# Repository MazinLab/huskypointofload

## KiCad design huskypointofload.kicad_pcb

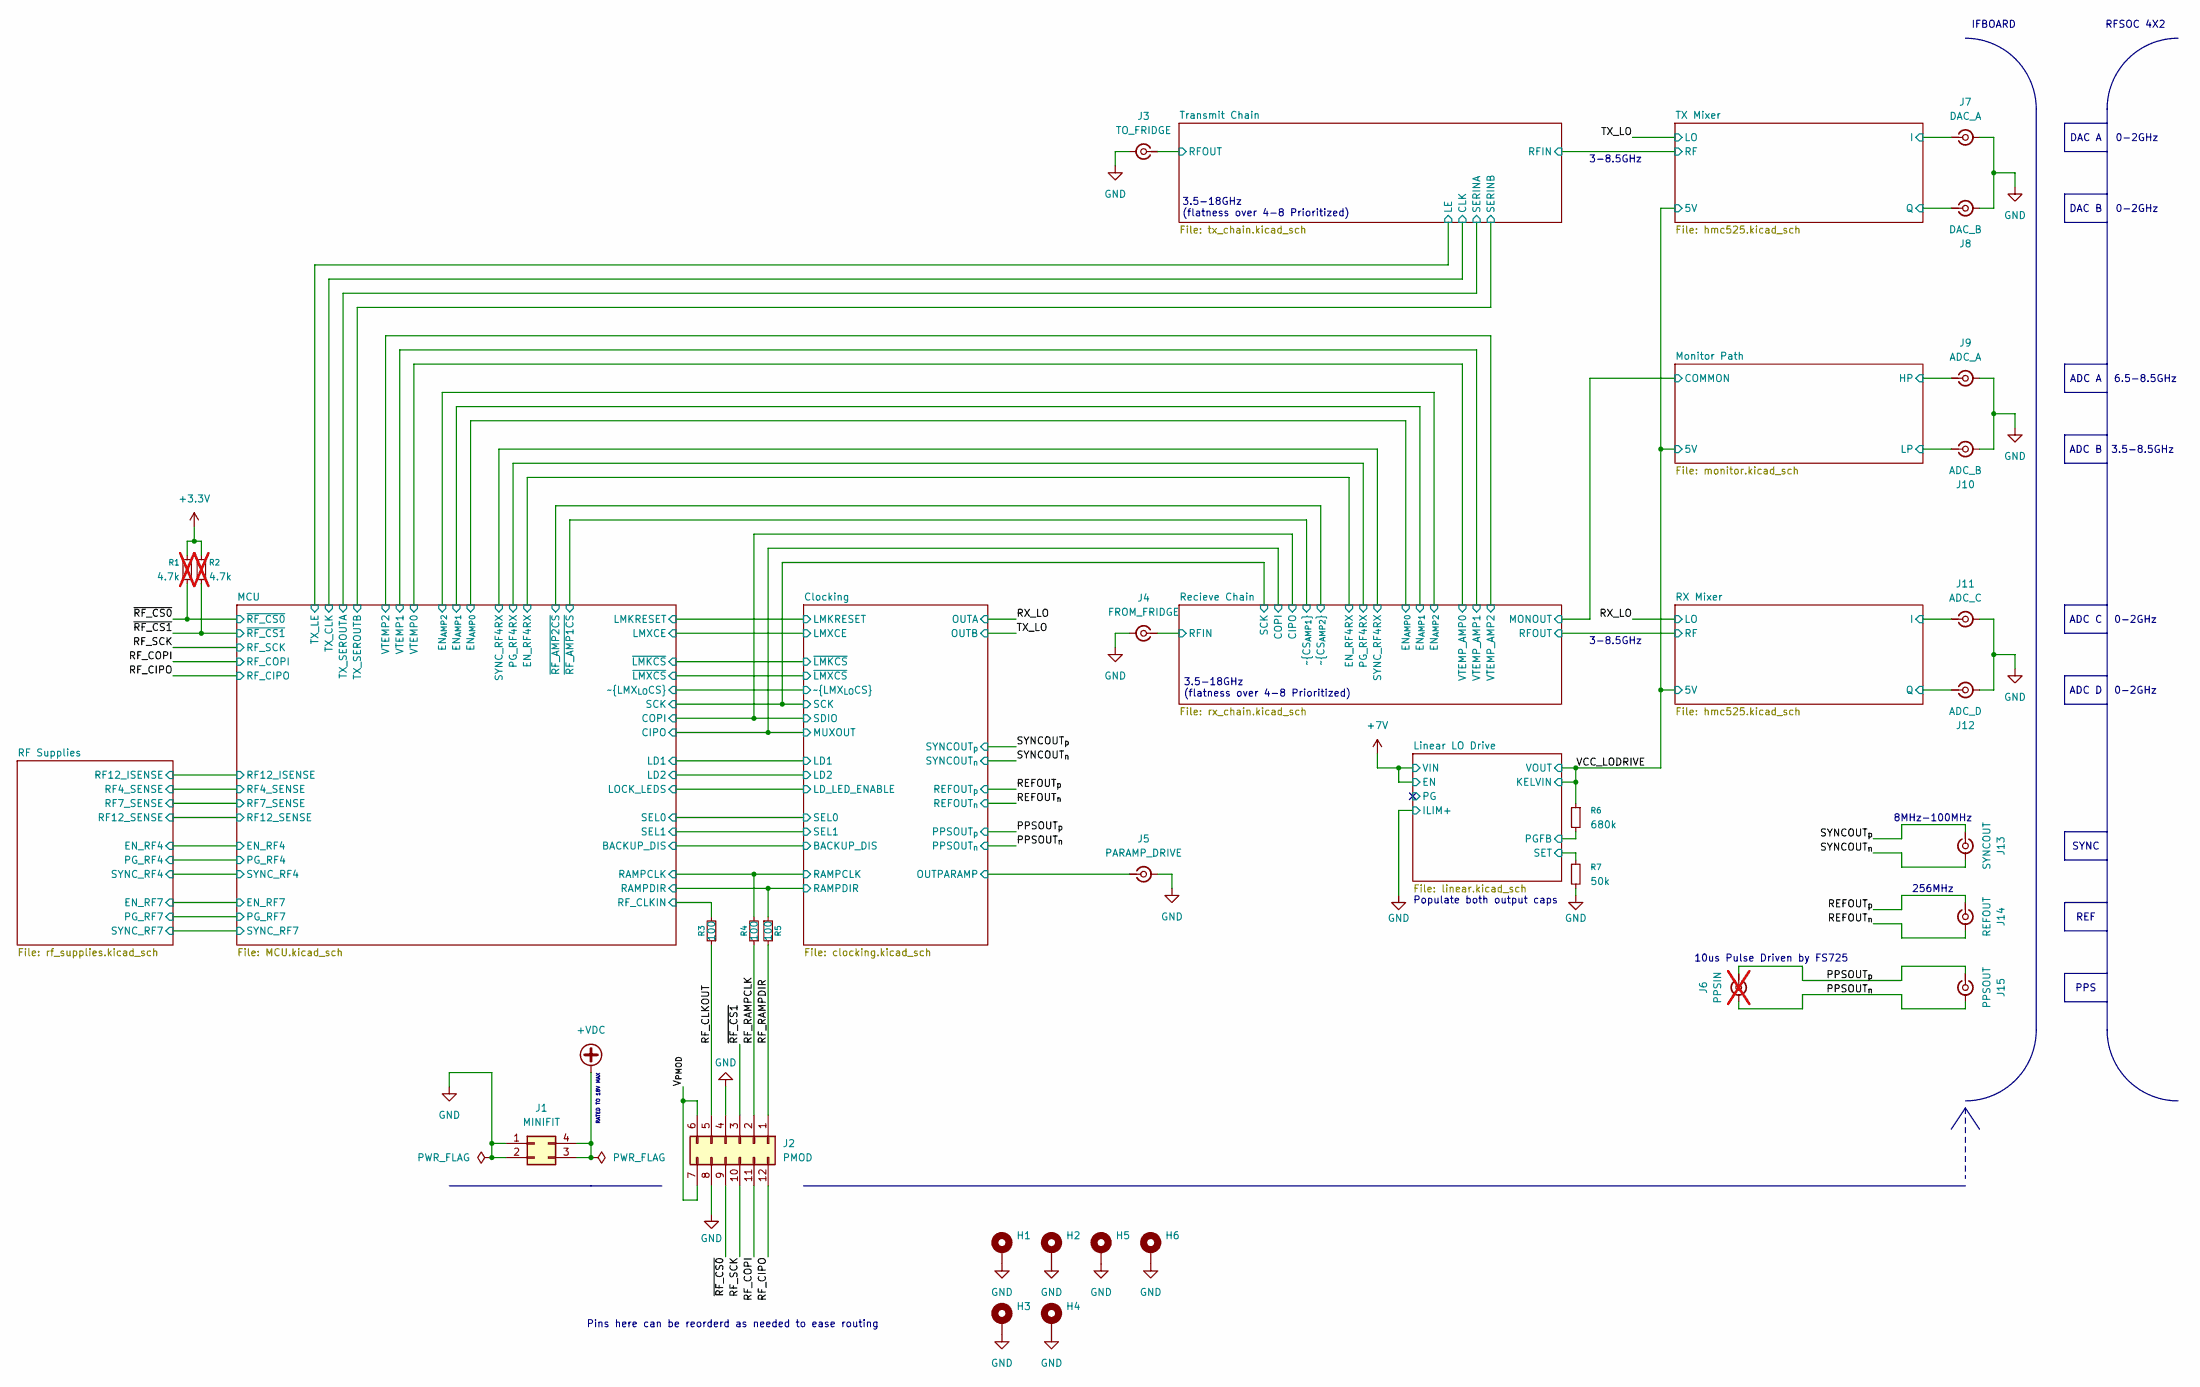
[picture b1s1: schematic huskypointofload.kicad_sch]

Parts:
H1, H2, H3, H4, H5, H6: MountingHole_Pad; MountingHole_3.5mm_Pad_TopBottom
J1: MINIFIT; Molex_Mini-Fit_Jr_5566-04A_2x02_P4.20mm_Vertical
J2: PMOD; PinSocket_2x06_P2.54mm_Horizontal
J3: TO_FRIDGE; SMP_V_SM
J4: FROM_FRIDGE; SMP_V_SM
J5: PARAMP_DRIVE; SMP_V_EL
J6: PPSIN; WR-MMCX_Wuerth_66012102111404_Vertical; not fitted
J7: DAC_A; SMP_EL
J8: DAC_B; SMP_EL
J9: ADC_A; SMP_EL
J10: ADC_B; SMP_EL
J11: ADC_C; SMP_EL
J12: ADC_D; SMP_EL
J13: SYNCOUT; SMP_EL
J14: REFOUT; SMP_EL
J15: PPSOUT; SMP_EL
R1, R2: 4.7k; R_0402_1005Metric; not fitted
R3, R4, R5: 100; R_0402_1005Metric
R6: 680k; R_0402_1005Metric; DIGIKEY_PN 13-RC0402FR-13453KLCT-ND
R7: 50k; R_0402_1005Metric; DIGIKEY_PN YAG4374CT-ND

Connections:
+3.3V: R1.1, R2.1; also elsewhere on the board
+VDC: J1.3, J1.4; also elsewhere on the board
/Clocking/OUTPARAMP: J5.1 (In); also elsewhere on the board
/Clocking/RAMPCLK: R4.2; also elsewhere on the board
/Clocking/RAMPDIR: R5.1; also elsewhere on the board
/Linear LO Drive/PGFB: R6.2; also elsewhere on the board
/Linear LO Drive/SET: R7.1; also elsewhere on the board
/MCU/RF_CLKIN: R3.2; also elsewhere on the board
/Monitor Path/HP: J9.1 (In); also elsewhere on the board
/Monitor Path/LP: J10.1 (In); also elsewhere on the board
/PPSOUT_{n}: J6.2 (Ext), J15.2 (Ext); also elsewhere on the board
/PPSOUT_{p}: J6.1 (In), J15.1 (In); also elsewhere on the board
/REFOUT_{n}: J14.2 (Ext); also elsewhere on the board
/REFOUT_{p}: J14.1 (In); also elsewhere on the board
/RF_CIPO: J2.12; also elsewhere on the board
/RF_CLKOUT: J2.5, R3.1
/RF_COPI: J2.11; also elsewhere on the board
/RF_RAMPCLK: J2.2, R4.1
/RF_RAMPDIR: J2.1, R5.2
/RF_SCK: J2.10; also elsewhere on the board
/RX Mixer/I: J11.1 (In); also elsewhere on the board
/RX Mixer/Q: J12.1 (In); also elsewhere on the board
/Recieve Chain/RFIN: J4.1 (In); also elsewhere on the board
/SYNCOUT_{n}: J13.2 (Ext); also elsewhere on the board
/SYNCOUT_{p}: J13.1 (In); also elsewhere on the board
/TX Mixer/I: J7.1 (In); also elsewhere on the board
/TX Mixer/Q: J8.1 (In); also elsewhere on the board
/Transmit Chain/RFOUT: J3.1 (In); also elsewhere on the board
/VCC_LODRIVE: R6.1; also elsewhere on the board
/V_{PMOD}: J2.6, J2.7
/~RF_CS0: J2.9, R1.2; also elsewhere on the board
/~RF_CS1: J2.3, R2.2; also elsewhere on the board
GND: H1.1 (1_1), H2.1 (1_1), H3.1 (1_1), H4.1 (1_1), H5.1 (1_1), H6.1 (1_1), J1.1, J1.2, J2.4, J2.8, J3.2 (Ext), J4.2 (Ext), J5.2 (Ext), J7.2 (Ext), J8.2 (Ext), J9.2 (Ext), J10.2 (Ext), J11.2 (Ext), J12.2 (Ext), R7.2; also elsewhere on the board

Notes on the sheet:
DAC B
3.5-18GHz (flatness over 4-8 Prioritized)
RATED TO 18V MAX
REF
0-2GHz
10us Pulse Driven by FS725
3-8.5GHz
256MHz
ADC A
RFSOC 4X2
ADC B
8MHz-100MHz
IFBOARD
SYNC
Pins here can be reorderd as needed to ease routing
3.5-8.5GHz
ADC D
PPS
DAC A
Populate both output caps
6.5-8.5GHz
ADC C

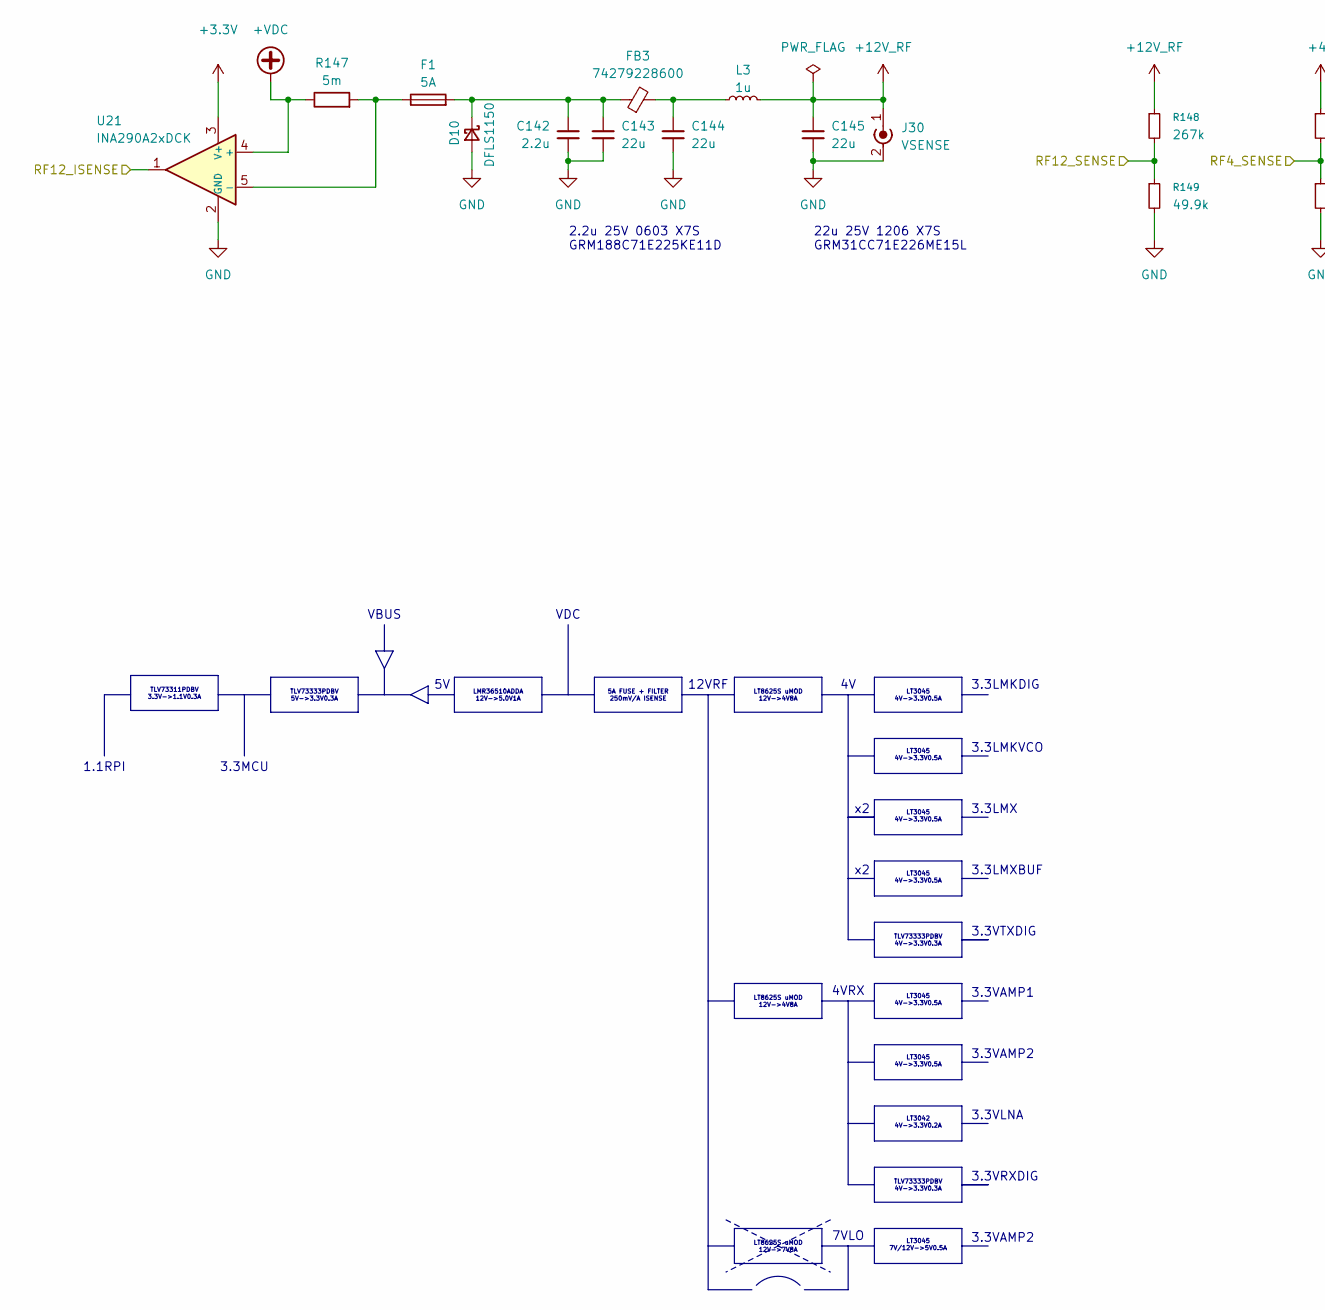
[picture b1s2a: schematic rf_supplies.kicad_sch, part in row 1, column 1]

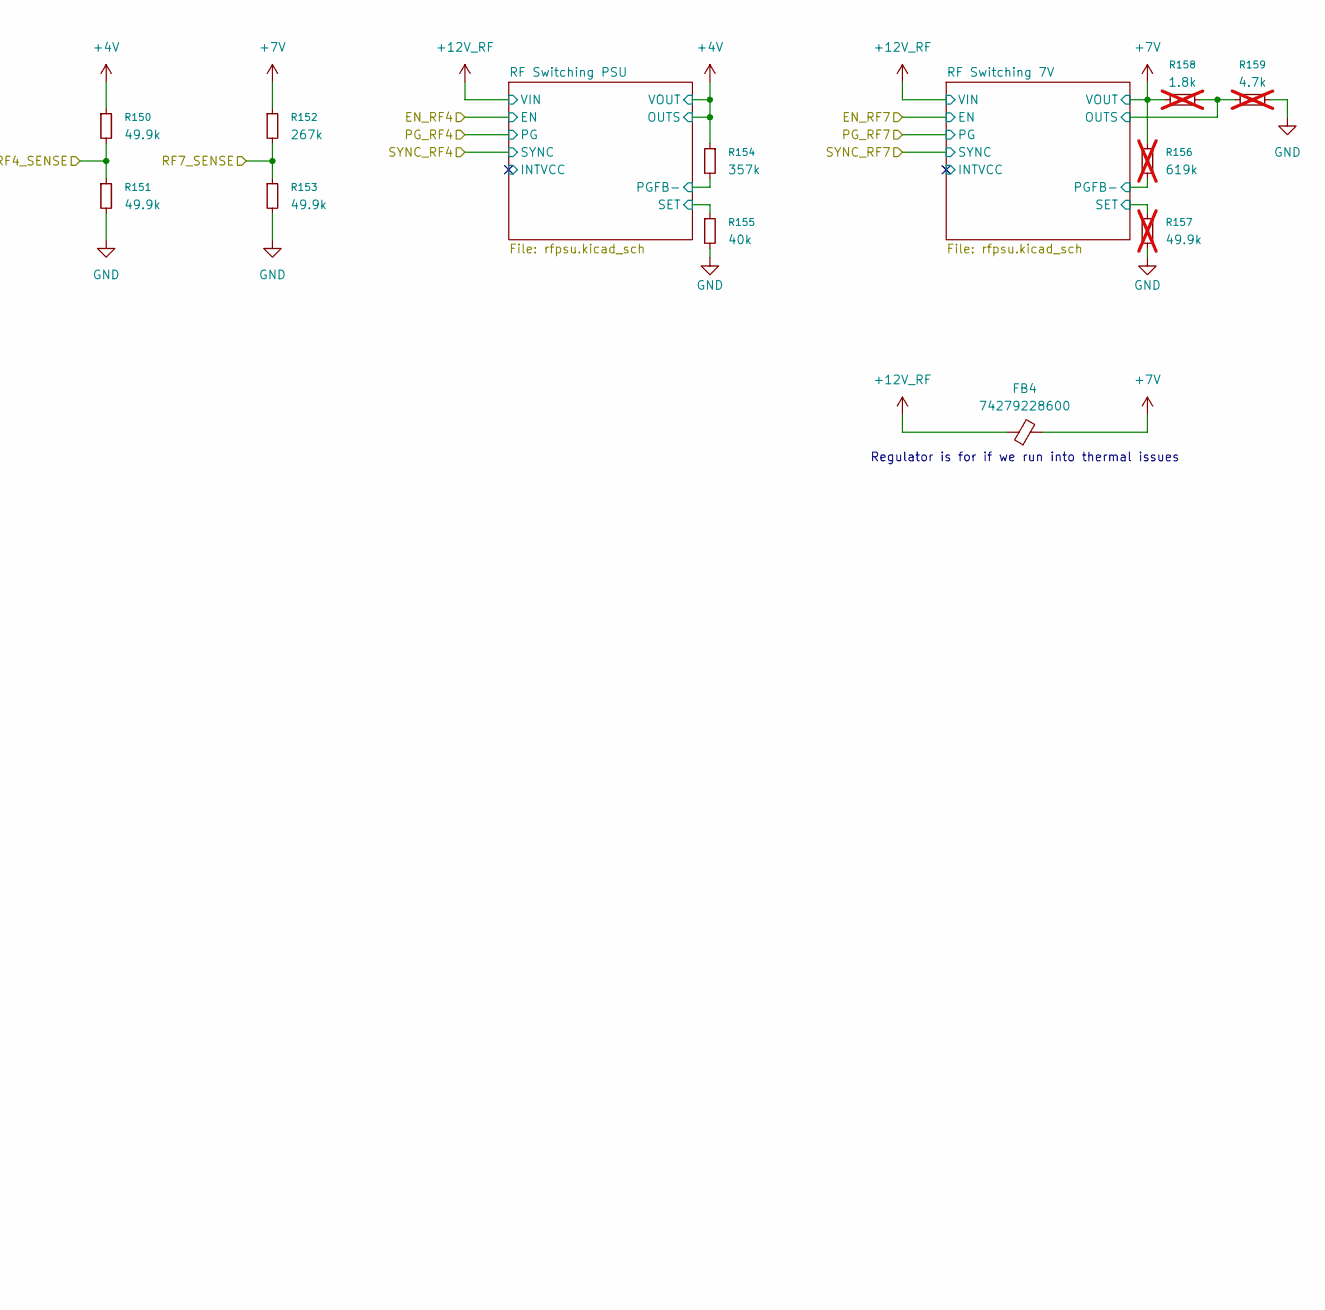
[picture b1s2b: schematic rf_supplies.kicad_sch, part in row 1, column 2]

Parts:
C142: 2.2u; C_0603_1608Metric; DIGIKEY_PN 490-12732-1-ND
C143, C144, C145: 22u; C_1206_3216Metric; DIGIKEY_PN 490-GRM31CC71E226ME15LCT-ND
D10: DFLS1150; D_PowerDI-123; DIGIKEY_PN DFLS1150DICT-ND
F1: 5A; Fuseholder_Littelfuse_Nano2_157x; DIGIKEY_PN F2973CT-ND
FB3, FB4: 74279228600; L_0603_1608Metric; DIGIKEY_PN 732-6119-1-ND
J30: VSENSE; SMA_Amphenol_132134-10_Vertical; DIGIKEY_PN ARF2755-ND
L3: 1u; L_Bourns_SRR1260; DIGIKEY_PN SRR1260-1R0YCT-ND
R147: 5m; R_2512_6332Metric; DIGIKEY_PN YAG2145CT-ND
R148, R152: 267k; R_0402_1005Metric; DIGIKEY_PN 2019-RN73R1ETTP2673B25CT-ND
R149, R150, R151, R153: 49.9k; R_0402_1005Metric; DIGIKEY_PN YAG4394CT-ND
R154: 357k; R_0402_1005Metric; DIGIKEY_PN YAG3129CT-ND
R155: 40k; R_0402_1005Metric; DIGIKEY_PN 738-RNCF0402BTE40K0CT-ND
R156: 619k; R_0402_1005Metric; DIGIKEY_PN YAG3129CT-ND; not fitted
R157: 49.9k; R_0402_1005Metric; not fitted
R158: 1.8k; R_0402_1005Metric; not fitted
R159: 4.7k; R_0402_1005Metric; not fitted
U21: INA290A2xDCK; SOT-353_SC-70-5; DIGIKEY_PN 296-INA290A2IDCKRCT-ND

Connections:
+3.3V: U21.3 (V+); also elsewhere on the board
+4V: R150.1, R154.1; also elsewhere on the board
+7V: FB4.2, R152.1, R156.1, R158.1; also elsewhere on the board
+12V_RF: C145.1, FB4.1, J30.1 (In), L3.1, R148.1; also elsewhere on the board
+VDC: R147.1, U21.4 (+); also elsewhere on the board
/MCU/RF4_SENSE: R150.2, R151.1; also elsewhere on the board
/MCU/RF7_SENSE: R152.2, R153.1; also elsewhere on the board
/MCU/RF12_ISENSE: U21.1; also elsewhere on the board
/MCU/RF12_SENSE: R148.2, R149.1; also elsewhere on the board
/RF Supplies/RF Switching 7V/OUTS: R158.2, R159.1; also elsewhere on the board
/RF Supplies/RF Switching 7V/PGFB-: R156.2; also elsewhere on the board
/RF Supplies/RF Switching 7V/SET: R157.1; also elsewhere on the board
/RF Supplies/RF Switching PSU/PGFB-: R154.2; also elsewhere on the board
/RF Supplies/RF Switching PSU/SET: R155.1; also elsewhere on the board
GND: C142.2, C143.2, C144.2, C145.2, D10.2 (A), J30.2 (Ext), R149.2, R151.2, R153.2, R155.2, R157.2, R159.2, U21.2 (GND); also elsewhere on the board
unnamed: C144.1, FB3.2, L3.2
unnamed: C142.1, C143.1, D10.1 (K), F1.2, FB3.1
unnamed: F1.1, R147.2, U21.5 (-)

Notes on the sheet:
12VRF
LT3045 4V->3.3V0.5A
22u 25V 1206 X7S GRM31CC71E226ME15L
TLV73311PDBV 3.3V->1.1V0.3A
LT8625S uMOD 12V->4V8A
TLV73333PDBV 4V->3.3V0.3A
3.3VRXDIG
3.3VAMP2
VBUS
3.3VAMP1
3.3LMX
7VLO
VDC
TLV73333PDBV 5V->3.3V0.3A
1.1RPI
3.3LMKDIG
LT3042 4V->3.3V0.2A
3.3VLNA
3.3LMKVCO
4VRX
Regulator is for if we run into thermal issues
3.3VTXDIG
2.2u 25V 0603 X7S GRM188C71E225KE11D
LMR36510ADDA 12V->5.0V1A
3.3MCU
LT3045 7V/12V->5V0.5A
3.3LMXBUF
5A FUSE + FILTER 250mV/A ISENSE
LT8625S uMOD 12V->7V8A

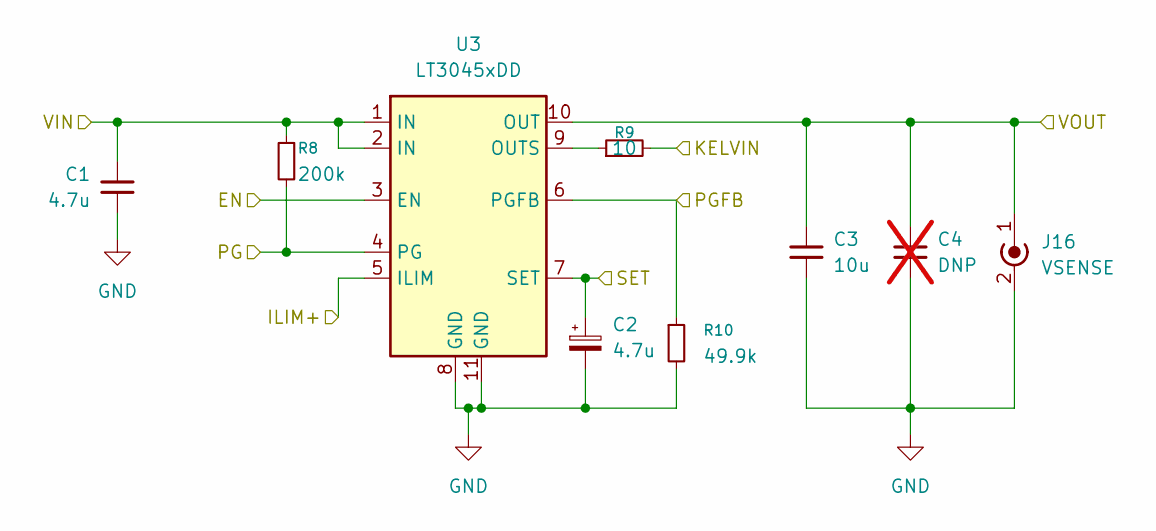
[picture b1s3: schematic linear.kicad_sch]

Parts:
C1: 4.7u; C_1206_3216Metric; DIGIKEY_PN 490-GRM31CZ72A475ME11LCT-ND
C2: 4.7u; CP_EIA-2012-15_AVX-P; DIGIKEY_PN 718-TMCP1A475KTRFCT-ND
C3: 10u; C_0603_1608Metric; DIGIKEY_PN 490-10727-1-ND
C4: DNP; C_0201_0603Metric; not fitted
J16: VSENSE; SMA_Amphenol_132134-10_Vertical; DIGIKEY_PN ARF2755-ND
R8: 200k; R_0402_1005Metric; DIGIKEY_PN 311-200KJRCT-ND
R9: 10; R_0402_1005Metric; DIGIKEY_PN 311-10.0LRCT-ND
R10: 49.9k; R_0402_1005Metric; DIGIKEY_PN YAG4394CT-ND
U3: LT3045xDD; DFN-10-1EP_3x3mm_P0.5mm_EP1.65x2.38mm; DIGIKEY_PN 505-LT3045EDD#PBF-ND

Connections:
+3.3VA_LMKDIG: C3.1, C4.1, J16.1 (In), R9.2, U3.10 (OUT); also elsewhere on the board
+4V: C1.1, R8.1, U3.1 (IN), U3.2 (IN), U3.3 (EN); also elsewhere on the board
/Clocking/LMK04828/Linear POL LMK DIG/PG: R8.2, U3.4 (PG)
/Clocking/LMK04828/Linear POL LMK DIG/PGFB: R10.1, U3.6 (PGFB); also elsewhere on the board
/Clocking/LMK04828/Linear POL LMK DIG/SET: C2.1, U3.7 (SET); also elsewhere on the board
GND: C1.2, C2.2, C3.2, C4.2, J16.2 (Ext), R10.2, U3.5 (ILIM), U3.8 (GND), U3.11 (GND); also elsewhere on the board
unnamed: R9.1, U3.9 (OUTS)

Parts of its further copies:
C9, C154, C160, C164, C168, C188, C236, C270, C278: 4.7u; C_1206_3216Metric; DIGIKEY_PN 490-GRM31CZ72A475ME11LCT-ND
C10, C155, C161, C165, C169, C189, C237, C271, C279: 4.7u; CP_EIA-2012-15_AVX-P; DIGIKEY_PN 718-TMCP1A475KTRFCT-ND
C11, C156, C162, C166, C170, C190, C238, C272, C280: 10u; C_0603_1608Metric; DIGIKEY_PN 490-10727-1-ND
C12, C157, C163, C167, C171, C191, C239, C273, C281: DNP; C_0201_0603Metric; not fitted
J17, J33, J36, J37, J38, J39, J42, J44, J45: VSENSE; SMA_Amphenol_132134-10_Vertical; DIGIKEY_PN ARF2755-ND
R11, R185, R193, R196, R199, R219, R254, R264, R267: 200k; R_0402_1005Metric; DIGIKEY_PN 311-200KJRCT-ND
R12, R186, R194, R197, R200, R220, R255, R265, R268: 10; R_0402_1005Metric; DIGIKEY_PN 311-10.0LRCT-ND
R13, R187, R195, R198, R201, R221, R256, R266, R269: 49.9k; R_0402_1005Metric; DIGIKEY_PN YAG4394CT-ND
U9, U22, U23, U24, U25, U32, U35, U41, U45: LT3045xDD; DFN-10-1EP_3x3mm_P0.5mm_EP1.65x2.38mm; DIGIKEY_PN 505-LT3045EDD#PBF-ND

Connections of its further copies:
+4V: C9.1, C154.1, C160.1, C188.1, C236.1, R11.1, R185.1, R193.1, R219.1, R254.1, U9.1 (IN), U9.2 (IN), U9.3 (EN), U22.1 (IN), U22.2 (IN), U22.3 (EN), U23.1 (IN), U23.2 (IN), U23.3 (EN), U32.1 (IN), U32.2 (IN), U32.3 (EN), U35.1 (IN), U35.2 (IN), U35.3 (EN); also elsewhere on the board
+7V: C164.1, R196.1, U24.1 (IN), U24.2 (IN), U24.3 (EN); also elsewhere on the board
/Clocking/LMK04828/+3.3VA_LMKCGVCO: C156.1, C157.1, J33.1 (In), R186.2, U22.10 (OUT); also elsewhere on the board
/Clocking/LMK04828/Linear POL LMK VCO/PG: R185.2, U22.4 (PG)
/Clocking/LMK04828/Linear POL LMK VCO/PGFB: R187.1, U22.6 (PGFB); also elsewhere on the board
/Clocking/LMK04828/Linear POL LMK VCO/SET: C155.1, U22.7 (SET); also elsewhere on the board
/Clocking/LMX2594/+3.3VA_LMX: C11.1, C12.1, J17.1 (In), R12.2, U9.10 (OUT); also elsewhere on the board
/Clocking/LMX2594/Linear POL LMX BUF/PG: R254.2, U35.4 (PG)
/Clocking/LMX2594/Linear POL LMX BUF/PGFB: R256.1, U35.6 (PGFB); also elsewhere on the board
/Clocking/LMX2594/Linear POL LMX BUF/SET: C237.1, U35.7 (SET); also elsewhere on the board
/Clocking/LMX2594/Linear POL LMX/PG: R11.2, U9.4 (PG)
/Clocking/LMX2594/Linear POL LMX/PGFB: R13.1, U9.6 (PGFB); also elsewhere on the board
/Clocking/LMX2594/Linear POL LMX/SET: C10.1, U9.7 (SET); also elsewhere on the board
/Clocking/LMX2594_PARAMP/+3.3VA_LMX: C190.1, C191.1, J39.1 (In), R220.2, U32.10 (OUT); also elsewhere on the board
/Clocking/LMX2594_PARAMP/Linear POL LMX BUF/PG: R193.2, U23.4 (PG)
/Clocking/LMX2594_PARAMP/Linear POL LMX BUF/PGFB: R195.1, U23.6 (PGFB); also elsewhere on the board
/Clocking/LMX2594_PARAMP/Linear POL LMX BUF/SET: C161.1, U23.7 (SET); also elsewhere on the board
/Clocking/LMX2594_PARAMP/Linear POL LMX/PG: R219.2, U32.4 (PG)
/Clocking/LMX2594_PARAMP/Linear POL LMX/PGFB: R221.1, U32.6 (PGFB); also elsewhere on the board
/Clocking/LMX2594_PARAMP/Linear POL LMX/SET: C189.1, U32.7 (SET); also elsewhere on the board
/Clocking/LMX Single Ended Matching A1/+3.3VA_LMXBUF: C162.1, C163.1, J36.1 (In), R194.2, U23.10 (OUT); also elsewhere on the board
/Clocking/LMX Single Ended Matching A/+3.3VA_LMXBUF: C238.1, C239.1, J42.1 (In), R255.2, U35.10 (OUT); also elsewhere on the board
/Linear LO Drive/PG: R196.2, U24.4 (PG)
/Linear LO Drive/PGFB: R198.1, U24.6 (PGFB); also elsewhere on the board
/Linear LO Drive/SET: C165.1, U24.7 (SET); also elsewhere on the board
/Recieve Chain/+4V_RX: C168.1, C270.1, C278.1, R199.1, R264.1, R267.1, U25.1 (IN), U25.2 (IN), U25.3 (EN), U41.1 (IN), U41.2 (IN), U41.3 (EN), U45.1 (IN), U45.2 (IN), U45.3 (EN); also elsewhere on the board
/Recieve Chain/Linear POL AMP1/PG: R264.2, U41.4 (PG)
/Recieve Chain/Linear POL AMP1/PGFB: R266.1, U41.6 (PGFB); also elsewhere on the board
/Recieve Chain/Linear POL AMP1/SET: C271.1, U41.7 (SET); also elsewhere on the board
/Recieve Chain/Linear POL LMK AMP2/PG: R267.2, U45.4 (PG)
/Recieve Chain/Linear POL LMK AMP2/PGFB: R269.1, U45.6 (PGFB); also elsewhere on the board
/Recieve Chain/Linear POL LMK AMP2/SET: C279.1, U45.7 (SET); also elsewhere on the board
/Recieve Chain/Linear POL LMK VCO/KELVIN: C170.1, C171.1, J38.1 (In), R200.2, U25.10 (OUT); also elsewhere on the board
/Recieve Chain/Linear POL LMK VCO/PG: R199.2, U25.4 (PG)
/Recieve Chain/Linear POL LMK VCO/PGFB: R201.1, U25.6 (PGFB); also elsewhere on the board
/Recieve Chain/Linear POL LMK VCO/SET: C169.1, U25.7 (SET); also elsewhere on the board
/Recieve Chain/VCC_AMP1: C272.1, C273.1, J44.1 (In), R265.2, U41.10 (OUT); also elsewhere on the board
/Recieve Chain/VCC_AMP2: C280.1, C281.1, J45.1 (In), R268.2, U45.10 (OUT); also elsewhere on the board
/VCC_LODRIVE: C166.1, C167.1, J37.1 (In), R197.2, U24.10 (OUT); also elsewhere on the board
GND: C9.2, C10.2, C11.2, C12.2, C154.2, C155.2, C156.2, C157.2, C160.2, C161.2, C162.2, C163.2, C164.2, C165.2, C166.2, C167.2, C168.2, C169.2, C170.2, C171.2, C188.2, C189.2, C190.2, C191.2, C236.2, C237.2, C238.2, C239.2, C270.2, C271.2, C272.2, C273.2, C278.2, C279.2, C280.2, C281.2, J17.2 (Ext), J33.2 (Ext), J36.2 (Ext), J37.2 (Ext), J38.2 (Ext), J39.2 (Ext), J42.2 (Ext), J44.2 (Ext), J45.2 (Ext), R13.2, R187.2, R195.2, R198.2, R201.2, R221.2, R256.2, R266.2, R269.2, U9.5 (ILIM), U9.8 (GND), U9.11 (GND), U22.5 (ILIM), U22.8 (GND), U22.11 (GND), U23.5 (ILIM), U23.8 (GND), U23.11 (GND), U24.5 (ILIM), U24.8 (GND), U24.11 (GND), U25.5 (ILIM), U25.8 (GND), U25.11 (GND), U32.5 (ILIM), U32.8 (GND), U32.11 (GND), U35.5 (ILIM), U35.8 (GND), U35.11 (GND), U41.5 (ILIM), U41.8 (GND), U41.11 (GND), U45.5 (ILIM), U45.8 (GND), U45.11 (GND); also elsewhere on the board
unnamed: R12.1, U9.9 (OUTS)
unnamed: R186.1, U22.9 (OUTS)
unnamed: R194.1, U23.9 (OUTS)
unnamed: R197.1, U24.9 (OUTS)
unnamed: R200.1, U25.9 (OUTS)
unnamed: R220.1, U32.9 (OUTS)
unnamed: R255.1, U35.9 (OUTS)
unnamed: R265.1, U41.9 (OUTS)
unnamed: R268.1, U45.9 (OUTS)

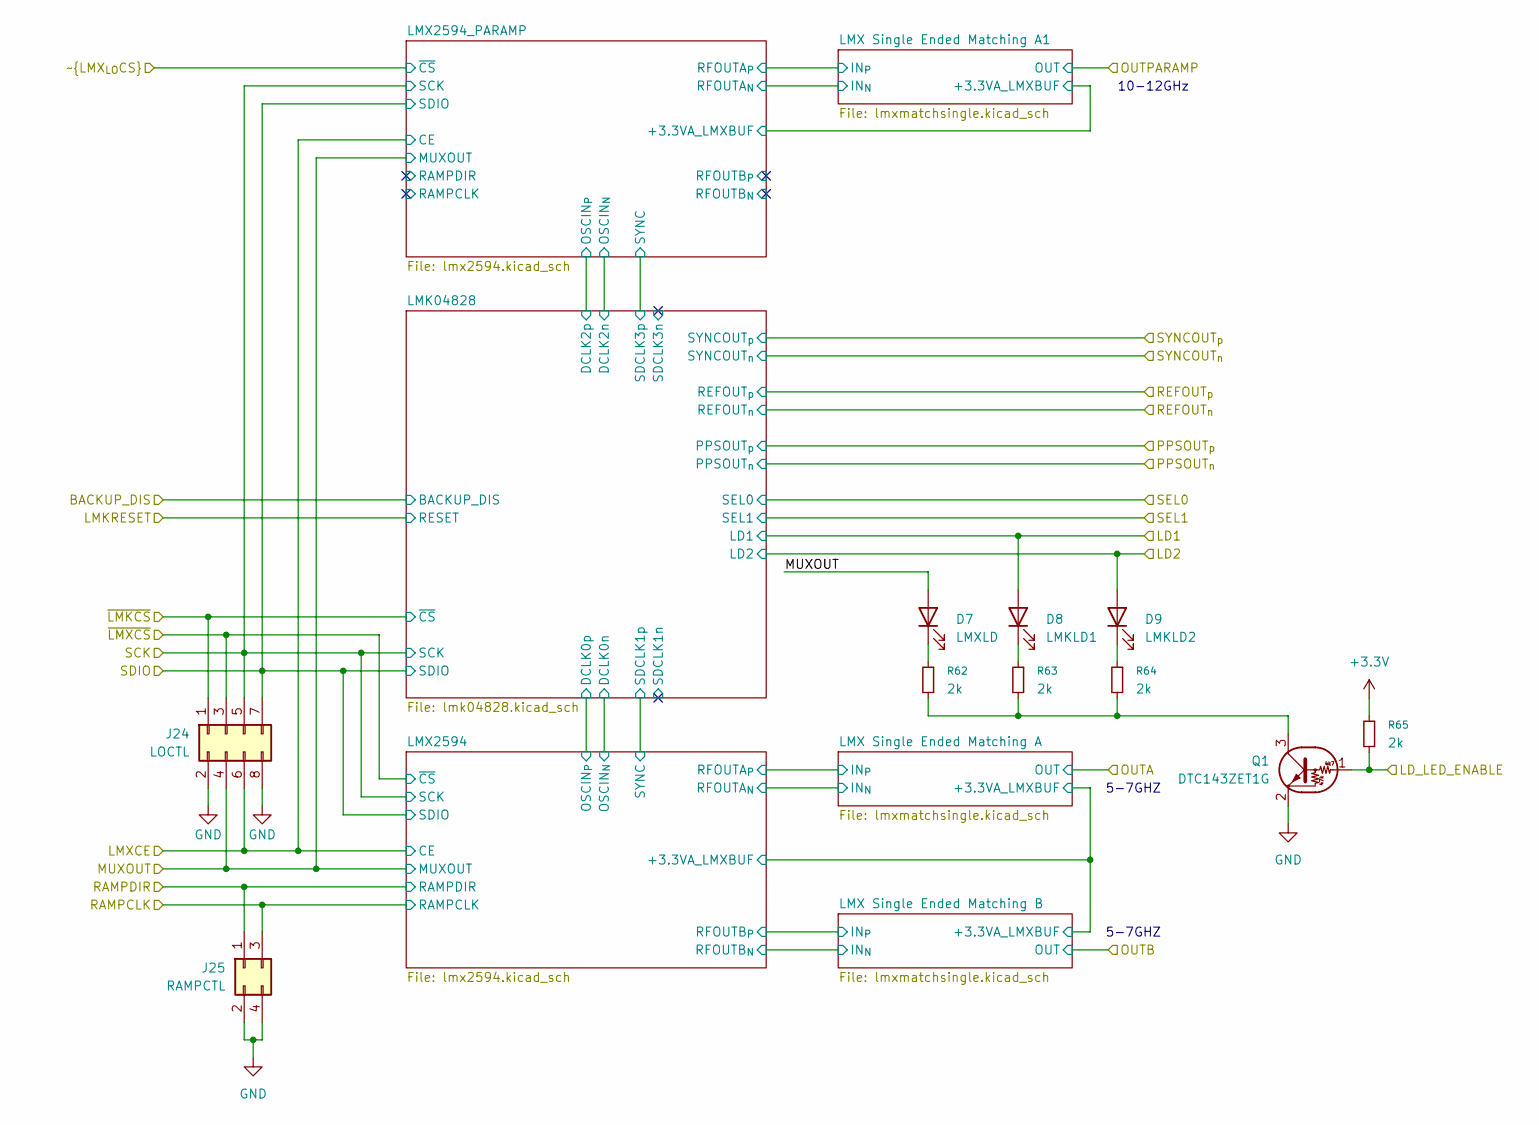
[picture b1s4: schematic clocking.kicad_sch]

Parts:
D7: LMXLD; LED_0402_1005Metric
D8: LMKLD1; LED_0402_1005Metric
D9: LMKLD2; LED_0402_1005Metric
J24: LOCTL; PinHeader_2x04_P2.54mm_Vertical
J25: RAMPCTL; PinHeader_2x02_P2.54mm_Vertical
Q1: DTC143ZET1G; SOT-416
R62, R63, R64, R65: 2k; R_0402_1005Metric

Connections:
+3.3V: R65.1; also elsewhere on the board
/Clocking/LD1: D8.2 (A); also elsewhere on the board
/Clocking/LD2: D9.2 (A); also elsewhere on the board
/Clocking/LD_LED_ENABLE: Q1.1 (B), R65.2; also elsewhere on the board
/Clocking/LMXCE: J24.6; also elsewhere on the board
/Clocking/MUXOUT: D7.2 (A), J24.4; also elsewhere on the board
/Clocking/RAMPCLK: J25.3; also elsewhere on the board
/Clocking/RAMPDIR: J25.1; also elsewhere on the board
/Clocking/~LMKCS: J24.1; also elsewhere on the board
/Clocking/~LMXCS: J24.3; also elsewhere on the board
/Recieve Chain/CIPO: J24.7; also elsewhere on the board
/Recieve Chain/SCK: J24.5; also elsewhere on the board
GND: J24.2, J24.8, J25.2, J25.4, Q1.2 (E); also elsewhere on the board
unnamed: D7.1 (K), R62.1
unnamed: D8.1 (K), R63.1
unnamed: D9.1 (K), R64.1
unnamed: Q1.3 (C), R62.2, R63.2, R64.2

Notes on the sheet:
10-12GHz
5-7GHZ

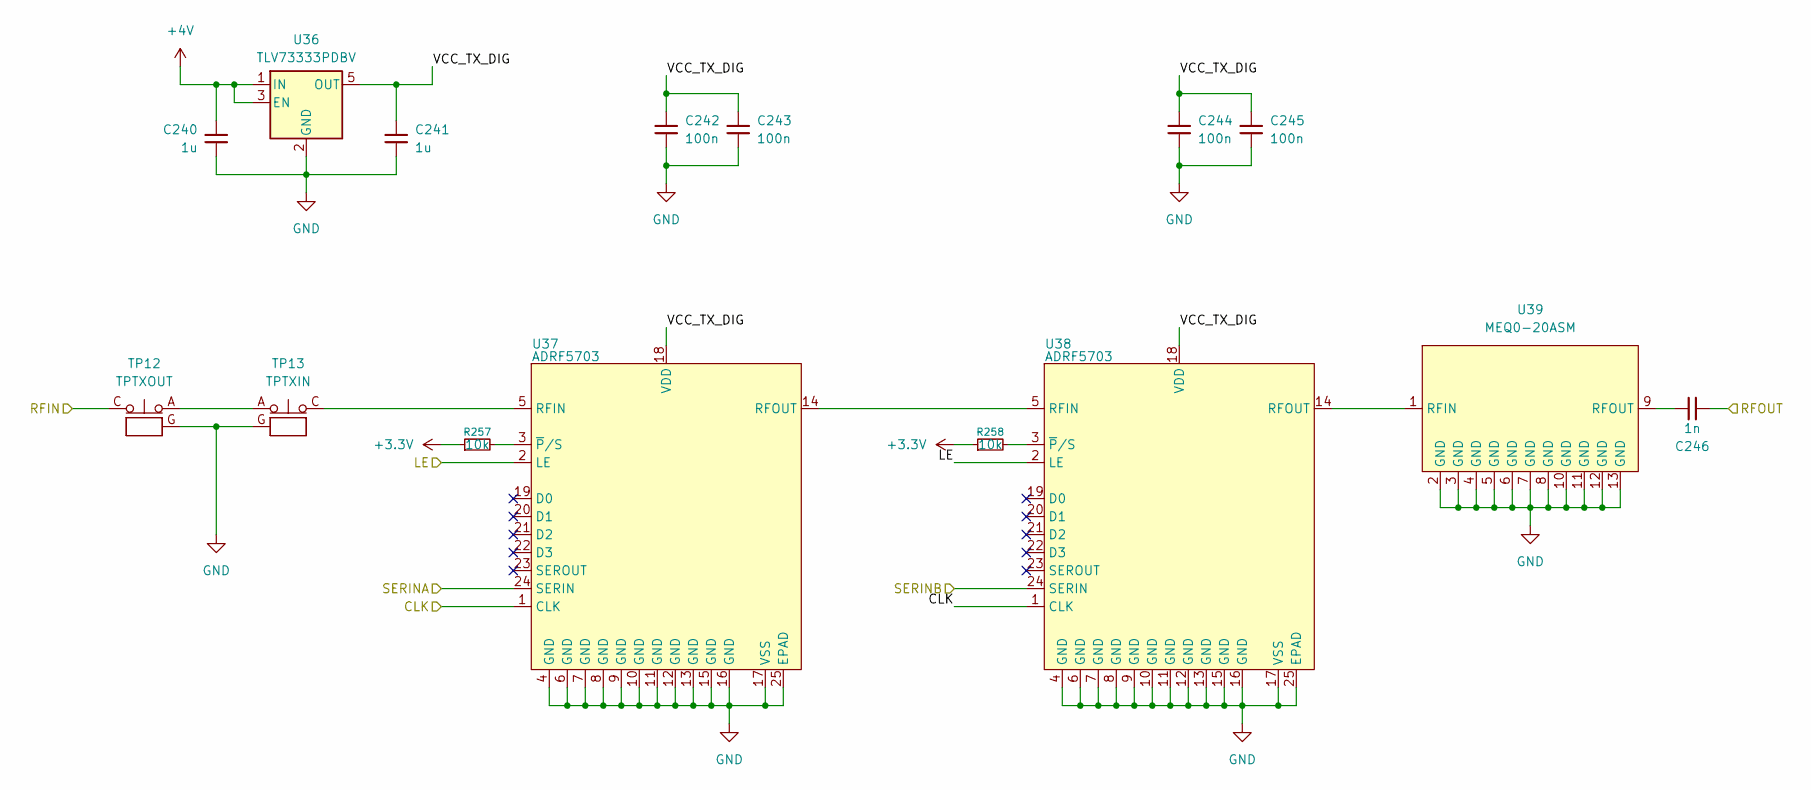
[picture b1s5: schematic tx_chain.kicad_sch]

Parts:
C240, C241: 1u; C_0402_1005Metric
C242, C243, C244, C245: 100n; C_0402_1005Metric; DIGIKEY_PN 490-14603-1-ND
C246: 1n; C_0201_0603Metric
R257, R258: 10k; R_0402_1005Metric
TP12: TPTXOUT; CoaxialSwitch_Hirose_MS-156C3_Horizontal
TP13: TPTXIN; CoaxialSwitch_Hirose_MS-156C3_Horizontal
U36: TLV73333PDBV; SOT-23-5
U37, U38: ADRF5703; LGA-24_CC-24-20
U39: MEQ0-20ASM

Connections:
+3.3V: R257.1, R258.1; also elsewhere on the board
+4V: C240.1, U36.1 (IN), U36.3 (EN); also elsewhere on the board
/MCU/TX_SEROUTA: U37.24 (SERIN); also elsewhere on the board
/MCU/TX_SEROUTB: U38.24 (SERIN); also elsewhere on the board
/TX Mixer/RF: TP12.C; also elsewhere on the board
/Transmit Chain/CLK: U37.1 (CLK), U38.1 (CLK); also elsewhere on the board
/Transmit Chain/LE: U37.2 (LE), U38.2 (LE); also elsewhere on the board
/Transmit Chain/RFOUT: C246.1; also elsewhere on the board
/Transmit Chain/VCC_TX_DIG: C241.1, C242.1, C243.1, C244.1, C245.1, U36.5 (OUT), U37.18 (VDD), U38.18 (VDD)
GND: C240.2, C241.2, C242.2, C243.2, C244.2, C245.2, TP12.G, TP13.G, U36.2 (GND), U37.4 (GND), U37.6 (GND), U37.7 (GND), U37.8 (GND), U37.9 (GND), U37.10 (GND), U37.11 (GND), U37.12 (GND), U37.13 (GND), U37.15 (GND), U37.16 (GND), U37.17 (VSS), U37.25 (EPAD), U38.4 (GND), U38.6 (GND), U38.7 (GND), U38.8 (GND), U38.9 (GND), U38.10 (GND), U38.11 (GND), U38.12 (GND), U38.13 (GND), U38.15 (GND), U38.16 (GND), U38.17 (VSS), U38.25 (EPAD), U39.2 (GND), U39.3 (GND), U39.4 (GND), U39.5 (GND), U39.6 (GND), U39.7 (GND), U39.8 (GND), U39.10 (GND), U39.11 (GND), U39.12 (GND), U39.13 (GND); also elsewhere on the board
unnamed: TP12.A, TP13.A
unnamed: TP13.C, U37.5 (RFIN)
unnamed: U37.14 (RFOUT), U38.5 (RFIN)
unnamed: R257.2, U37.3 (~P/S)
unnamed: U38.14 (RFOUT), U39.1 (RFIN)
unnamed: R258.2, U38.3 (~P/S)
unnamed: C246.2, U39.9 (RFOUT)
